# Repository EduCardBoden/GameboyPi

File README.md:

# GameboyPi v1.2 – Raspberry-Pi-Zero-Handheld im Game-Boy-Color-Stil

Tragbarer Retro-Handheld mit eigener Trägerplatine (KiCad 10), 3D-druckbarem Gehäuse (OpenSCAD) und LiPo-Akku.
**Status: Design fertig und rechnerisch geprüft, aber noch nicht gebaut.** Siehe [Prüfstatus](documentation/testing.md) und [offene Risiken](#offene-technische-risiken).

| | |
|---|---|
| Rechner | Raspberry Pi Zero 2 W (Zero W / Zero kompatibel) |
| Display | 2,4" ILI9341 SPI, 320×240 (LAFVIN mit Touch ≈ MSP2402, Touch ungenutzt), 60 fps mit fbcp-ili9341 |
| Bedienung | D-Pad, A, B, Start, Select, Ein/Aus-Schiebeschalter (sicheres Herunterfahren), Lautstärkeknopf |
| Audio | 20-mm-Lautsprecher (PAM8302, 2,5 W) + 3,5-mm-Kopfhörerbuchse mit Lautsprecher-Abschaltung |
| Akku | LiPo 103450, 2000 mAh, PowerBoost 1000C (Micro-USB-Laden, Spielen beim Laden, Lade-LEDs) |
| Laufzeit | ca. 2 h typisch (1,5–2,7 h), [Rechnung](documentation/battery-runtime.md) |
| Gehäuse | 84 × 140 × 29,3 mm (Original-GBC: 78 × 133,5 × 27,4 mm), Design **„GBX – Game Boy Emulator“**: schwarz mit Fasen, Logo in Chrom-Silber/Lila vorne und hinten ([Vorschau](mechanical/previews/design_front.png), [Rückseite](mechanical/previews/design_back.png)) |
| Kosten | ca. 130 € ([Stückliste](bom/bill-of-materials.csv)) |
| Wartung | microSD seitlich, Mini-HDMI + Micro-USB-Daten oben, UART-Konsole (J8), 6 Testpunkte |

## Projektstruktur

```
GameboyPi/
├── README.md                     ← diese Datei
├── ARCHITECTURE.md               ← wie die Generator-Skripte zusammenhängen (Datenfluss, Build)
├── CLAUDE.md                     ← Arbeitsregeln für Claude Code
├── bestellung/                   ← Bestellpaket: Platine (JLCPCB), Bauteile, 3D-Druck (vom Build aktualisiert)
├── bom/bill-of-materials.csv     ← Stückliste mit Bezugsquellen und Preisen
├── electronics/
│   ├── kicad-project/            ← KiCad-Projekt + Generator-Skripte (design.py = zentrale Netzliste)
│   ├── gerber/                   ← Gerber + Bohrdaten + GameboyPi_Gerber.zip (zum Hersteller)
│   ├── schematics/               ← Schaltplan als PDF
│   └── assembly/                 ← Pick&Place-CSV, KiCad-BOM, Bestückungspläne (PDF), 3D-Renderings, STEP
├── mechanical/
│   ├── cad-source/               ← gameboy_pi_case.scad (parametrisch) + build.ps1 (Kollisionsprüfung, STL)
│   │   ├── logo/                 ← GBX-Logo: Originalbild, trace_logo.py (Vektorisierung), gbx_logo.scad
│   │   └── fonts/                ← Michroma (SIL Open Font License) für die Slogans
│   ├── stl/                      ← front, back, dpad, ab, startselect, knob + 4 Logo-Einlagen (silber/lila)
│   ├── step/                     ← dieselben Teile als STEP-Volumenkörper (FreeCAD, nicht im Git)
│   └── previews/                 ← Vorschaubilder
├── software/
│   ├── setup-guide.md            ← RetroPie-Einrichtung, Treiber, Tasten, Audio, Akku, Herunterfahren
│   └── configuration/            ← config.txt-Ergänzung, install.sh, Akku-Dienst
├── documentation/
│   ├── wiring.md                 ← Architektur, GPIO-Belegung, Modul-Pinouts, Abschaltlogik
│   ├── assembly-guide.md         ← Werkzeug, Lötreihenfolge, Druck, Endmontage
│   ├── testing.md                ← durchgeführte Prüfungen + Inbetriebnahme-Messplan
│   └── battery-runtime.md        ← Stromverbrauch, Laufzeit, Lade-/Entladeströme, Kabel
├── tools/freerouting/            ← Autorouter (wird von build.ps1 genutzt)
└── .vscode/                      ← Tasks: Strg+Shift+B baut alles
```

## Bauen (VS Code)

Den Ordner in VS Code öffnen, dann **Strg+Shift+B** („Alles bauen“). Alternativ einzeln über *Terminal → Task ausführen*:

- **Platine bauen (KiCad):** Schaltplan → Platine → Freerouting → ERC/DRC → Gerber, BOM, Pick&Place, PDFs, Renderings (~3 min)
- **Gehäuse bauen (OpenSCAD):** Kollisionsprüfung aller Bauteile gegen die Schalen → STLs → Vorschaubilder
- **Nur STLs exportieren**, **Platine in KiCad öffnen**, **Gehäuse in OpenSCAD öffnen**

Benötigt (installiert): KiCad 10.0, OpenSCAD 2021.01, Java 25 (Microsoft OpenJDK) für Freerouting 2.5.

## Komponenten- und Architekturentscheidungen

| Entscheidung | Begründung |
|---|---|
| **Pi Zero 2 W** kopfüber auf der Platinenrückseite | 4 Kerne (SNES/PS1 flüssig), gleiche Pinbelegung wie Zero/Zero W. Kopfüber wird das Gerät flacher, HDMI/USB zeigen zur Oberkante. |
| **2,4" ILI9341 SPI (LAFVIN ≈ MSP2402)** | Passt in die GBC-Breite. Der Linux-Treiber fbcp-ili9341 ist erprobt (DMA, 60 fps, geringe Latenz). Maße stammen aus der Herstellerzeichnung. Das bestellte Modul hat eine Touch-Folie (ungenutzt), das Gehäuse ist dafür 1,3 mm dicker (`lcd_touch`). |
| **Adafruit PowerBoost 1000C** statt TP4056 + MT3608 | Geprüftes Modul mit Load-Sharing (laden und spielen), festen 5,2 V (kein Einstell-Poti, das ab Werk 12 V liefern kann), EN-Eingang für die Abschaltlogik, LBO-Signal und Lade-LEDs. |
| **Soft-Power mit 2 × BS170** | Der Schalter trennt nicht hart. Er fordert das Herunterfahren an, und der Pi schaltet sich danach selbst ab. Schützt die SD-Karte. |
| **PWM-Audio + PAM8302 + Klinke mit Schaltkontakt** | Ein Audiopfad für beides: Kopfhörer bekommen Line-Pegel, der Lautsprecher bekommt Verstärker und Lautstärkepoti. Ein I2S-Verstärker (v1.0) kann keine Kopfhörer treiben. |
| **ADS1115** an VBAT/2 | Pi hat keinen ADC. Liefert Akkustand in % plus Abschaltung bei leerem Akku. |
| **Nur THT-Bauteile + Module** | Von Hand lötbar, keine SMD-Bestückung beim Hersteller nötig. |

## Stückliste (Kurzfassung, Details in `bom/bill-of-materials.csv`)

| Teil | ca. € |
|---|---|
| Raspberry Pi Zero 2 W (mit Stiftleiste) + 2×20-Buchse + Abstandsbolzen | 22,50 |
| microSD 32 GB | 7,00 |
| Display LAFVIN 2,4" (Touch) + M3-Abstandshalter | 16,80 |
| Adafruit PowerBoost 1000C | 22,00 |
| LiPo 103450 2000 mAh mit Schutz | 10,00 |
| Adafruit PAM8302 + Lautsprecher 20 mm | 7,00 |
| Adafruit ADS1115 | 15,00 |
| Taster, Schalter, Klinke, Poti, MOSFETs, Diode, LED, R/C, Stiftleisten | ≈ 7,20 |
| Leiterplatte (5 Stk. inkl. Versand) | 15,00 |
| Schrauben, Filament, Kleinmaterial, Acrylscheibe | ≈ 6,90 |
| **Summe** | **≈ 130 €** |

## Benötigtes Werkzeug

Temperaturgeregelter Lötkolben + Zinn + Flussmittel, Seitenschneider, Abisolierzange, Pinzette, **Multimeter**, Schraubendreher PH0/PH1, Messschieber, FDM-3D-Drucker. Optional: USB-UART-Adapter (3,3 V), Labornetzteil mit Strombegrenzung. Details in [assembly-guide.md](documentation/assembly-guide.md).

## Montage in Kurzform

1. Platine mit `electronics/gerber/GameboyPi_Gerber.zip` bestellen. Gehäuseteile aus `mechanical/stl/` drucken.
2. Vorderseite bestücken (R, C, LED, Taster, Schalter, Klinke), dann die Rückseite (R, D, Q, C1, Poti, UART, Pi-Buchse, Module).
3. **Inbetriebnahme ohne Pi** nach [testing.md](documentation/testing.md): Testpunkte messen, Abschaltlogik prüfen.
4. Display auf 4-mm-Abstandshalter setzen und verlöten.
5. Tasten, Lautsprecher und Platine in die Vorderschale legen, Akku in den Akkurahmen, Pi aufstecken, Rückschale verschrauben, Knopf aufstecken.
6. Software nach [setup-guide.md](software/setup-guide.md) einrichten.

## Erwartete Akkulaufzeit

≈ **2,1 h** typisch, 2,7 h bei Game Boy/NES mit WLAN aus, 1,5 h unter Dauervolllast. Laden mit 1 A in ≈ 2,5 h, Spielen währenddessen möglich. Rechenweg in [battery-runtime.md](documentation/battery-runtime.md).

## Offene technische Risiken

Ehrliche Liste dessen, was nur rechnerisch geprüft ist oder auf Annahmen beruht. **Vor der Bestellung von 5 Platinen lesen.**

1. **Nicht physisch gebaut oder gemessen.** ERC, DRC, Netzlistenvergleich und die Kollisionsprüfung im CAD sind bestanden. Es gab aber keinen Probedruck, keine Messung und keine Schaltungssimulation (SPICE) der Abschaltlogik.
2. **Soft-Power (v1.2 rechnerisch geklärt):** Die BS170-Schwelle (max. 3,0 V) ist bei **1 mA** Drainstrom spezifiziert (onsemi). Der EN-Pull-up im PowerBoost ist laut Adafruit-Schaltplan **R13 = 200 kΩ an VBAT**, Q1 muss also nur ≈ 21 µA ziehen, ~50× weniger als der Spezifikationsstrom. EN schaltet bei < 0,2 × VBAT ab (TI TPS61090). Restrisiko nur noch im Messplan (Punkt 2.2).
3. **gpio-poweroff:** Das Overlay ist für eine solche Abschaltung gedacht. Das Verhalten hängt aber von der Kernel-Version ab (RetroPie 4.8 / Buster). Falls GPIO4 nach dem Herunterfahren nicht low geht, kann ein systemd-Skript in `/lib/systemd/system-shutdown/` das übernehmen.
4. **PowerBoost-Grenze 1 A:** Geschätzte Spitzenlast ≈ 1 A (Pi-Last + laute Passagen). Seit v1.2 begrenzen R6/R7 = 47 kΩ die Lautsprecherleistung auf ≤ 0,5 W, damit sinkt der Audio-Spitzenstrom von ≈ 330 mA auf ≈ 120 mA (bei 5 V, 85 % Wirkungsgrad). Weitere Gegenmittel: C1 470 µF, WLAN aus.
5. **Gehäusemaße teils angenommen:** Display, Pi, PowerBoost, PAM8302 und ADS1115 stammen aus Herstellerdaten. **Nicht verifiziert** sind die Bauhöhen von Poti PTV09A-2 (≈ 11,5 mm angenommen), Klinke SJ1-3525N (5,2 mm), Elkos und Lautsprecher, ebenso die genaue Lage der PowerBoost-LEDs unter dem Lichtleiter. Die Öffnungen sind großzügig, trotzdem zuerst die Frontschale probedrucken.
6. **Kollisionsprüfung mit Hüllquadern:** Sie prüft vereinfachte Quader gegen die Schalen, keine exakten 3D-Modelle.
7. **Display-Variante:** Das Gehäuse ist auf das LAFVIN-Modul mit Touch-Folie (≈ MSP2402) ausgelegt (`lcd_touch = 1.3` in der `.scad`). Für ein MSP2401 ohne Touch `lcd_touch = 0` setzen und neu bauen. Die Dicke der Touch-Folie ist nur aus dem Produktbild abgeleitet, also vor dem Druck nachmessen. Andere 2,4"-Module (70,5 mm breit) passen nicht.
8. **PWM-Audio:** Leichtes Rauschen ist typisch. Kopfhörerpegel ist Line-Niveau (≈ −12 dB an 32 Ω), also eher leise. Die Kopfhörer-Lautstärke wird nur per Software geregelt, der Knopf regelt nur den Lautsprecher.
9. **Autorouting:** Freerouting hat geroutet. Engstellen gibt es zwischen den Pi-Pins mit 0,15 mm (fertigbar ab 0,127 mm). Ein menschlicher Review des Layouts (z. B. PWM-Audio neben SPI-Takt) ist empfehlenswert.
10. **Wärme:** Der Pi Zero 2 W im geschlossenen Gehäuse kann bei Dauerlast drosseln. Lüftungsschlitze sind vorhanden, eine thermische Simulation fehlt.
11. **Akkuanzeige im Bild** ist nicht umgesetzt (nur `/dev/shm/battery` + automatische Abschaltung). Ein Overlay (z. B. pngview) wäre der nächste Schritt.
12. **Software-Stack:** RetroPie 4.8 basiert auf Debian Buster (nicht mehr gepflegt). fbcp-ili9341 braucht diesen Legacy-Grafikstack. Die Bookworm-Alternative (mipi-dbi-spi) ist dokumentiert, aber langsamer.
13. **Akku-Steckerpolarität:** JST-PH-Akkus gibt es mit vertauschter Belegung. Vor dem Einstecken messen.
14. **Bestückungsdruck:** ca. 100 kosmetische Warnungen (Text auf Pads/Kante). Der Hersteller beschneidet sie, keine Funktion betroffen.
15. **Lieferlage Pi Zero 2 W (Stand 11.11.2026):** Bei BerryBase.at nicht lieferbar, bei Reichelt widersprüchliche Angaben (ein Artikel nennt „lieferbar“, die Shop-Suche „ab 22.12.2026“). Der Pi Zero W (langsamer) passt mechanisch und elektrisch. Details: `documentation/PURCHASING_COMPARISON.md`.
16. **ADS1115-Version:** Die Platine erwartet die Pinbelegung der **STEMMA-QT-Version** von Adafruit #1085. Ältere Lagerware (eine 10-polige Leiste) passt nicht. Vor dem Löten das Modul mit `wiring.md` vergleichen.

## Rechtliches

Nur eigene, rechtmäßig erworbene Spiele und BIOS-Dateien verwenden. Das Gehäuse ist vom Game Boy Color *inspiriert* und trägt das eigene „GBX“-Logo. Der Slogan „GAME BOY EMULATOR“ enthält die Marke „Game Boy“ (Nintendo). Für ein privates Einzelstück ist das unproblematisch. Wer Gehäuse oder Geräte verkaufen will, sollte den Slogan in `gameboy_pi_case.scad` (`back_silver_2d`) ändern.

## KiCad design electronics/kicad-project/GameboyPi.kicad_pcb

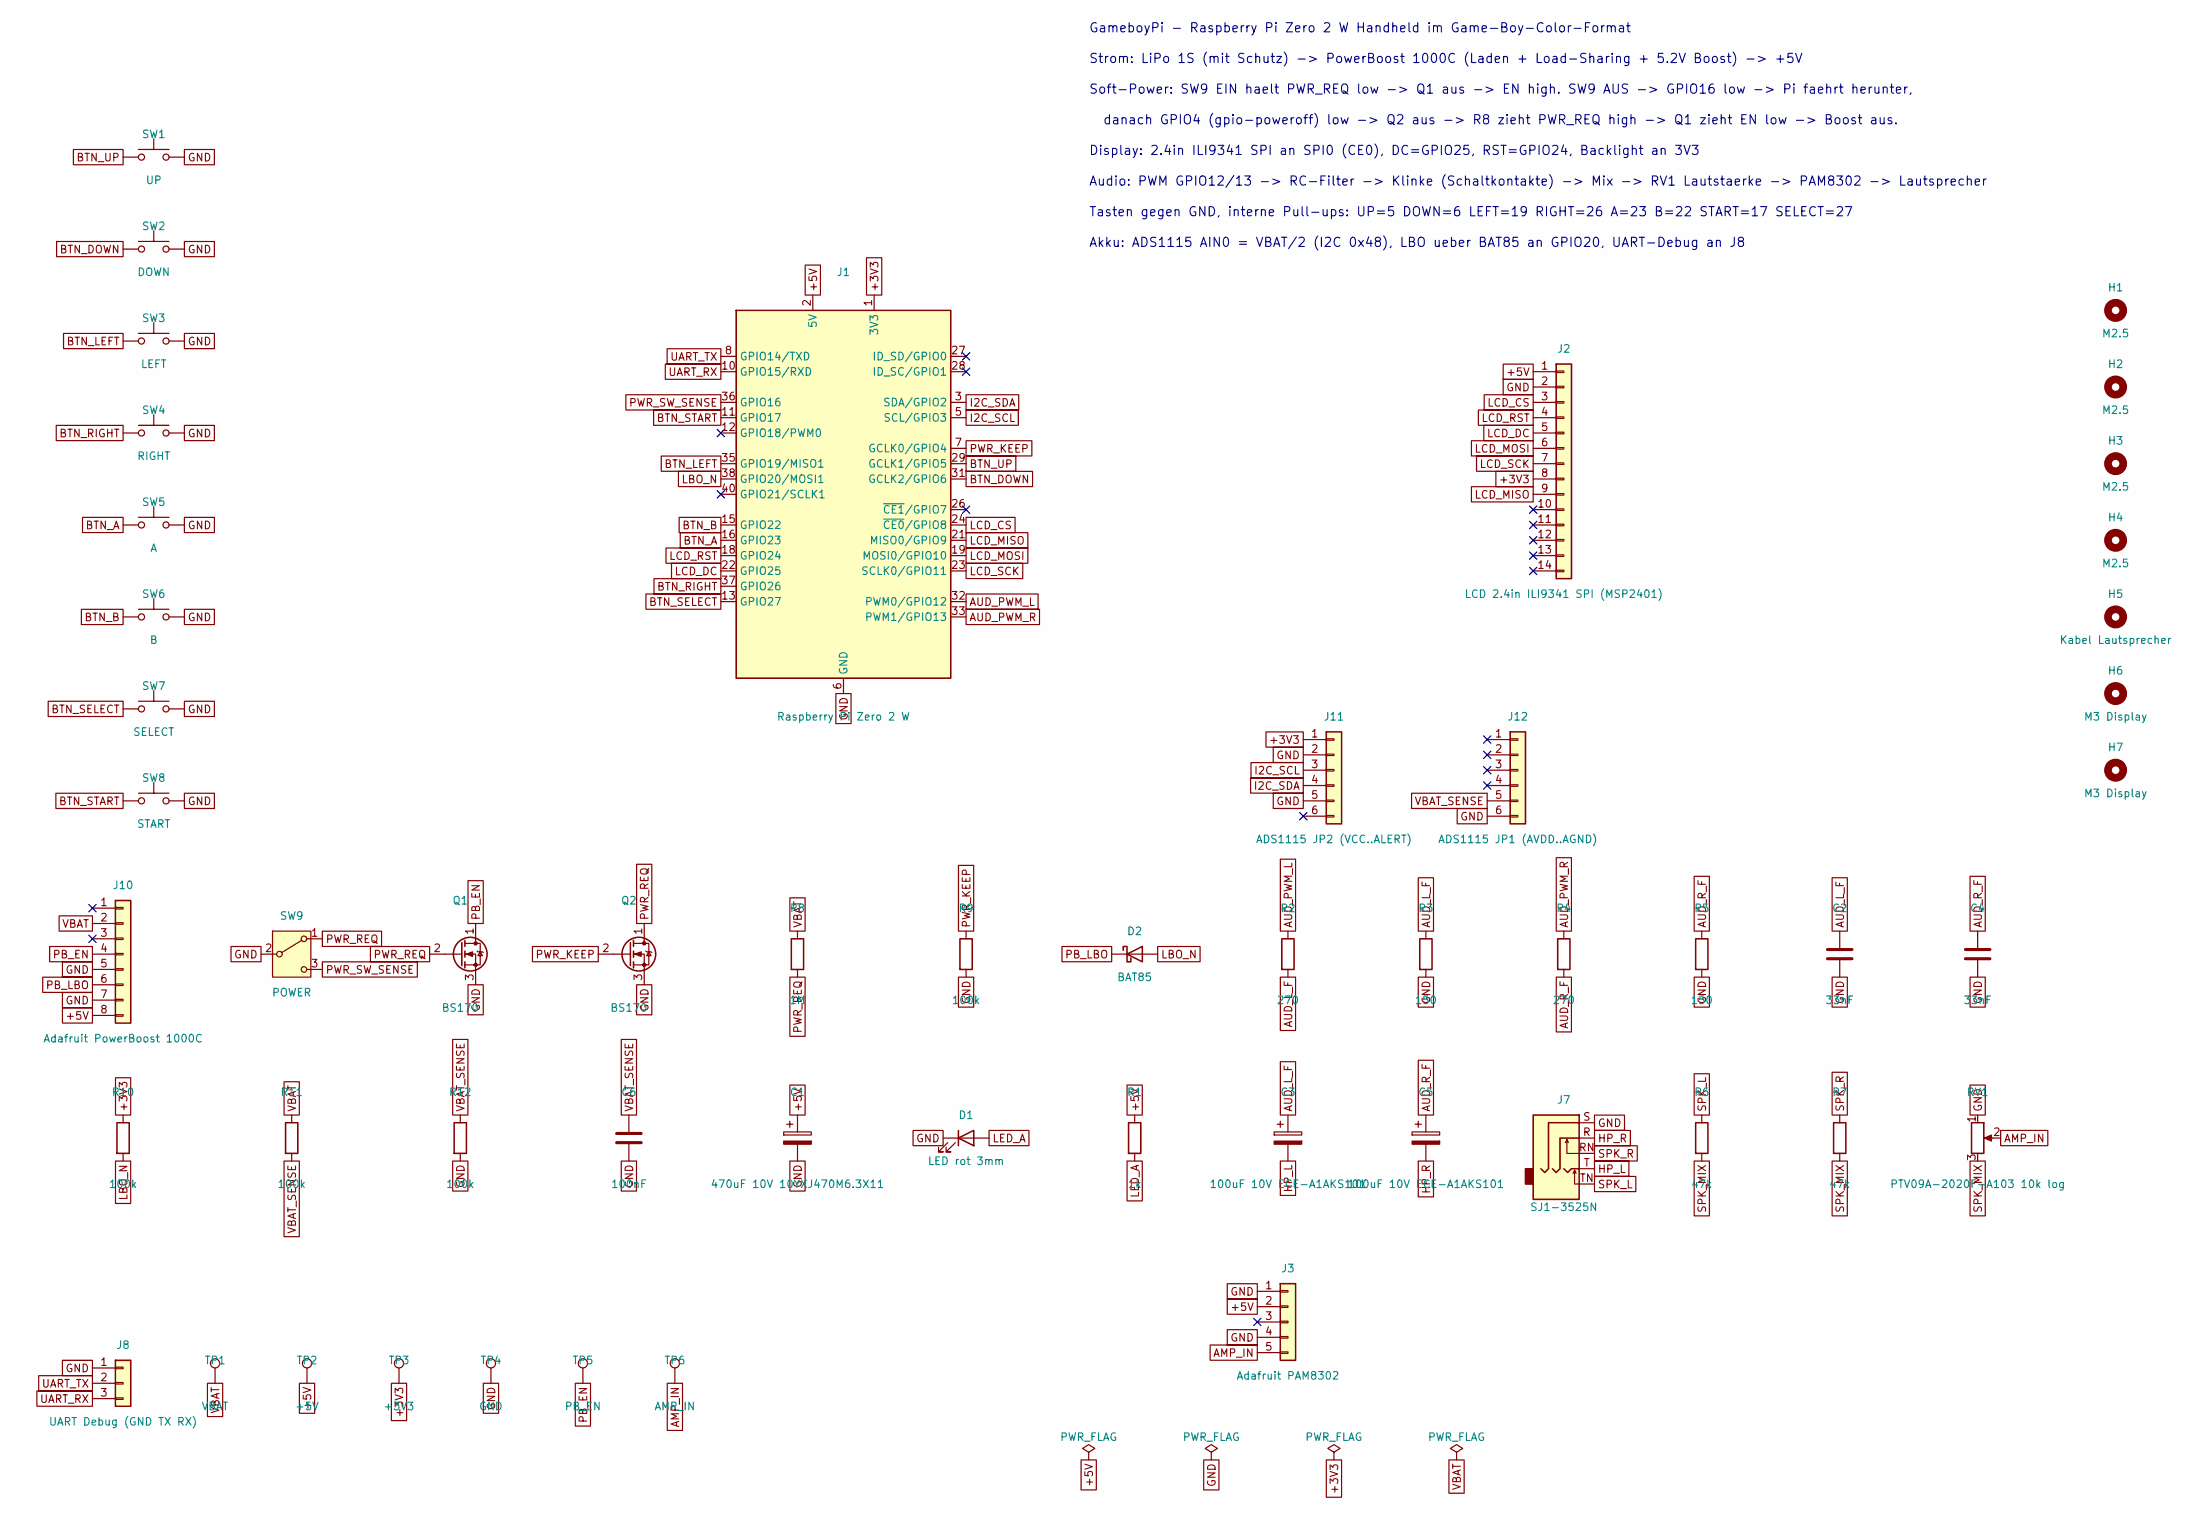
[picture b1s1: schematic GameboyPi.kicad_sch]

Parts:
C1: 470uF 10V 10YXJ470M6.3X11; CP_Radial_D6.3mm_P2.50mm
C2, C4: 33nF; C_Disc_D3.0mm_W1.6mm_P2.50mm
C3, C5: 100uF 10V ECE-A1AKS101; CP_Radial_D6.3mm_P2.50mm
C6: 100nF; C_Disc_D3.0mm_W1.6mm_P2.50mm
D1: LED rot 3mm; LED_D3.0mm
D2: BAT85; D_DO-35_SOD27_P7.62mm_Horizontal
H1, H2, H3, H4: M2.5; MountingHole_2.7mm_M2.5
H5: Kabel Lautsprecher; MountingHole_3.2mm_M3
H6, H7: M3 Display; MountingHole_3.2mm_M3
J1: Raspberry Pi Zero 2 W; Raspberry_Pi_Zero_Socketed_THT_FaceDown_MountingHoles
J2: LCD 2.4in ILI9341 SPI (MSP2401); PinHeader_1x14_P2.54mm_Vertical
J3: Adafruit PAM8302; PinHeader_1x05_P2.54mm_Vertical
J7: SJ1-3525N; Jack_3.5mm_CUI_SJ1-3525N_Horizontal
J8: UART Debug (GND TX RX); PinHeader_1x03_P2.54mm_Vertical
J10: Adafruit PowerBoost 1000C; PinHeader_1x08_P2.54mm_Vertical
J11: ADS1115 JP2 (VCC..ALERT); PinHeader_1x06_P2.54mm_Vertical
J12: ADS1115 JP1 (AVDD..AGND); PinHeader_1x06_P2.54mm_Vertical
Q1, Q2: BS170; TO-92_Inline_Wide
R1: 1k; R_Axial_DIN0207_L6.3mm_D2.5mm_P7.62mm_Horizontal
R2, R4: 270; R_Axial_DIN0207_L6.3mm_D2.5mm_P7.62mm_Horizontal
R3, R5: 150; R_Axial_DIN0207_L6.3mm_D2.5mm_P7.62mm_Horizontal
R6, R7: 47k; R_Axial_DIN0207_L6.3mm_D2.5mm_P7.62mm_Horizontal
R8: 1M; R_Axial_DIN0207_L6.3mm_D2.5mm_P7.62mm_Horizontal
R9, R10, R11, R12: 100k; R_Axial_DIN0207_L6.3mm_D2.5mm_P7.62mm_Horizontal
RV1: PTV09A-2020F-A103 10k log; Potentiometer_Bourns_PTV09A-2_Single_Horizontal
SW1: UP; SW_PUSH_6mm
SW2: DOWN; SW_PUSH_6mm
SW3: LEFT; SW_PUSH_6mm
SW4: RIGHT; SW_PUSH_6mm
SW5: A; SW_PUSH_6mm
SW6: B; SW_PUSH_6mm
SW7: SELECT; SW_PUSH_6mm
SW8: START; SW_PUSH_6mm
SW9: POWER; SW_Slide_SPDT_Angled_CK_OS102011MA1Q
TP1: VBAT; TestPoint_THTPad_D1.5mm_Drill0.7mm
TP2: +5V; TestPoint_THTPad_D1.5mm_Drill0.7mm
TP3: +3V3; TestPoint_THTPad_D1.5mm_Drill0.7mm
TP4: GND; TestPoint_THTPad_D1.5mm_Drill0.7mm
TP5: PB_EN; TestPoint_THTPad_D1.5mm_Drill0.7mm
TP6: AMP_IN; TestPoint_THTPad_D1.5mm_Drill0.7mm

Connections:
+3V3: J1.1 (3V3), J1.17 (3V3), J2.8, J11.1, R10.1, TP3.1
+5V: C1.1, J1.2 (5V), J1.4 (5V), J2.1, J3.2, J10.8, R1.1, TP2.1
AMP_IN: J3.5, RV1.2, TP6.1
AUD_L_F: C2.1, C3.1, R2.2, R3.1
AUD_PWM_L: J1.32 (PWM0/GPIO12), R2.1
AUD_PWM_R: J1.33 (PWM1/GPIO13), R4.1
AUD_R_F: C4.1, C5.1, R4.2, R5.1
BTN_A: J1.16 (GPIO23), SW5.1
BTN_B: J1.15 (GPIO22), SW6.1
BTN_DOWN: J1.31 (GCLK2/GPIO6), SW2.1
BTN_LEFT: J1.35 (GPIO19/MISO1), SW3.1
BTN_RIGHT: J1.37 (GPIO26), SW4.1
BTN_SELECT: J1.13 (GPIO27), SW7.1
BTN_START: J1.11 (GPIO17), SW8.1
BTN_UP: J1.29 (GCLK1/GPIO5), SW1.1
GND: C1.2, C2.2, C4.2, C6.2, D1.1 (K), J1.6 (GND), J1.9 (GND), J1.14 (GND), J1.20 (GND), J1.25 (GND), J1.30 (GND), J1.34 (GND), J1.39 (GND), J2.2, J3.1, J3.4, J7.S, J8.1, J10.5, J10.7, J11.2, J11.5, J12.6, Q1.3 (S), Q2.3 (S), R3.2, R5.2, R9.2, R12.2, RV1.1, SW1.2, SW2.2, SW3.2, SW4.2, SW5.2, SW6.2, SW7.2, SW8.2, SW9.2 (B), TP4.1
HP_L: C3.2, J7.T
HP_R: C5.2, J7.R
I2C_SCL: J1.5 (SCL/GPIO3), J11.3
I2C_SDA: J1.3 (SDA/GPIO2), J11.4
LBO_N: D2.2 (A), J1.38 (GPIO20/MOSI1), R10.2
LCD_CS: J1.24 (~CE0/GPIO8), J2.3
LCD_DC: J1.22 (GPIO25), J2.5
LCD_MISO: J1.21 (MISO0/GPIO9), J2.9
LCD_MOSI: J1.19 (MOSI0/GPIO10), J2.6
LCD_RST: J1.18 (GPIO24), J2.4
LCD_SCK: J1.23 (SCLK0/GPIO11), J2.7
LED_A: D1.2 (A), R1.2
PB_EN: J10.4, Q1.1 (D), TP5.1
PB_LBO: D2.1 (K), J10.6
PWR_KEEP: J1.7 (GCLK0/GPIO4), Q2.2 (G), R9.1
PWR_REQ: Q1.2 (G), Q2.1 (D), R8.2, SW9.1 (A)
PWR_SW_SENSE: J1.36 (GPIO16), SW9.3 (C)
SPK_L: J7.TN, R6.1
SPK_MIX: R6.2, R7.2, RV1.3
SPK_R: J7.RN, R7.1
UART_RX: J1.10 (GPIO15/RXD), J8.3
UART_TX: J1.8 (GPIO14/TXD), J8.2
VBAT: J10.2, R8.1, R11.1, TP1.1
VBAT_SENSE: C6.1, J12.5, R11.2, R12.1

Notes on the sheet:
GameboyPi - Raspberry Pi Zero 2 W Handheld im Game-Boy-Color-Format
Strom: LiPo 1S (mit Schutz) -> PowerBoost 1000C (Laden + Load-Sharing + 5.2V Boost) -> +5V
Soft-Power: SW9 EIN haelt PWR_REQ low -> Q1 aus -> EN high. SW9 AUS -> GPIO16 low -> Pi faehrt herunter,
danach GPIO4 (gpio-poweroff) low -> Q2 aus -> R8 zieht PWR_REQ high -> Q1 zieht EN low -> Boost aus.
Display: 2.4in ILI9341 SPI an SPI0 (CE0), DC=GPIO25, RST=GPIO24, Backlight an 3V3
Audio: PWM GPIO12/13 -> RC-Filter -> Klinke (Schaltkontakte) -> Mix -> RV1 Lautstaerke -> PAM8302 -> Lautsprecher
Tasten gegen GND, interne Pull-ups: UP=5 DOWN=6 LEFT=19 RIGHT=26 A=23 B=22 START=17 SELECT=27
Akku: ADS1115 AIN0 = VBAT/2 (I2C 0x48), LBO ueber BAT85 an GPIO20, UART-Debug an J8

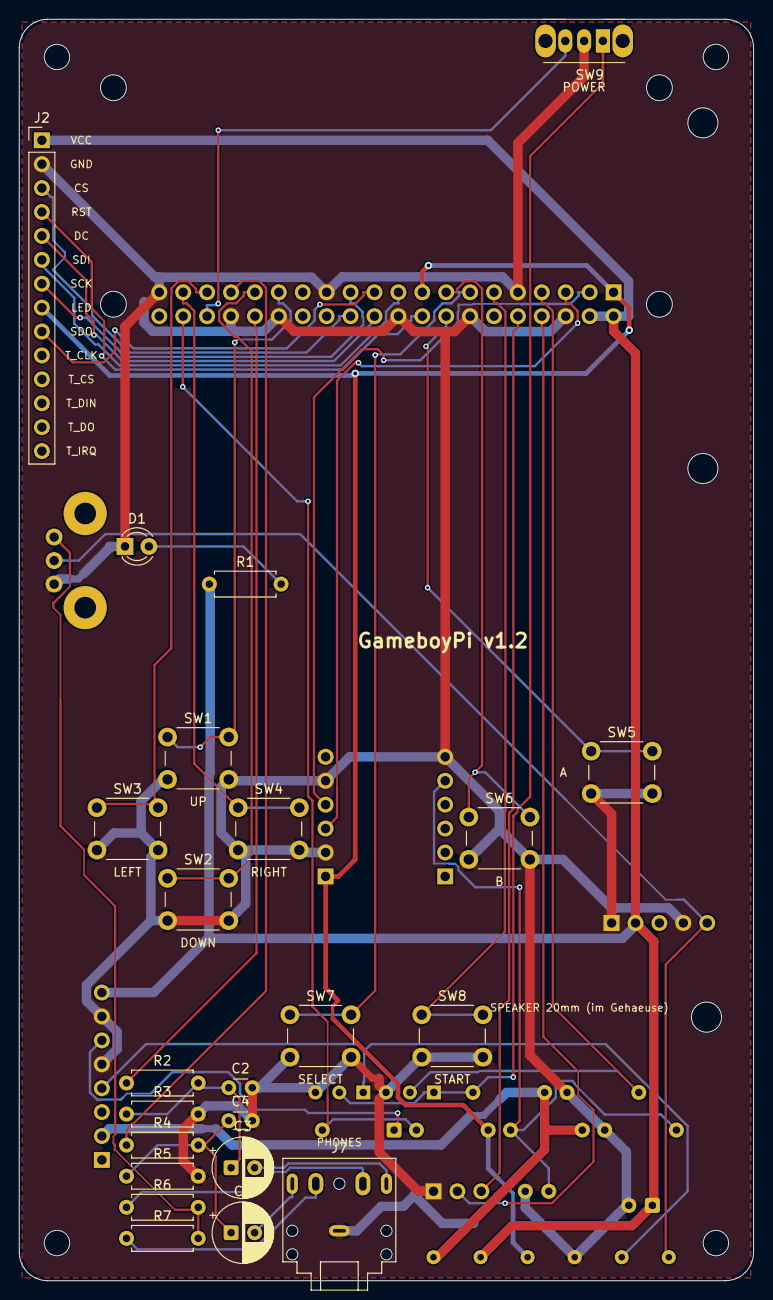
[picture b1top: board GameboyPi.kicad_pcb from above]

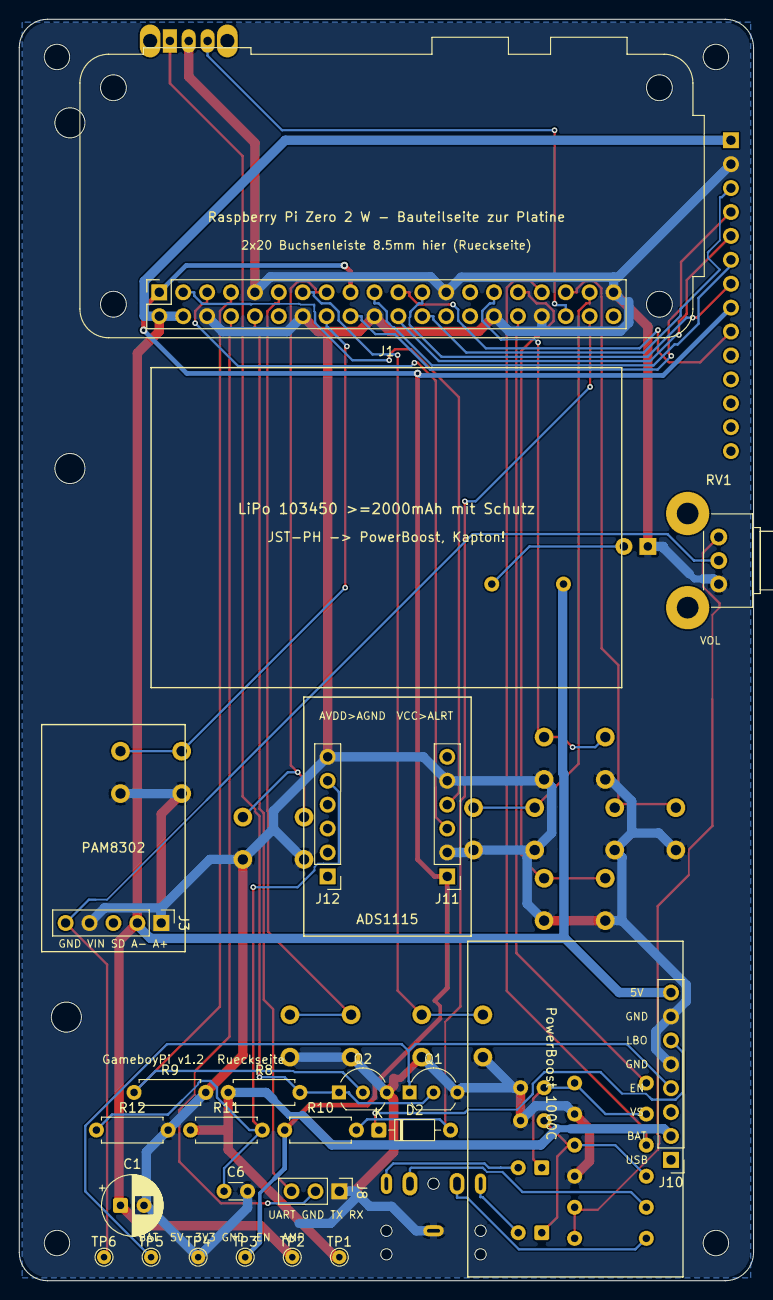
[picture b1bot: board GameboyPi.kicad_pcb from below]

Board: 2 copper layers, 78.0 x 134.0 mm, 53 parts (23 on the bottom side), 40 nets.

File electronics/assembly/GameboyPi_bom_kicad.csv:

"Reference","Value","Footprint","QUANTITY"
"C1","470uF 10V 10YXJ470M6.3X11","Capacitor_THT:CP_Radial_D6.3mm_P2.50mm","1"
"C2,C4","33nF","Capacitor_THT:C_Disc_D3.0mm_W1.6mm_P2.50mm","2"
"C3,C5","100uF 10V ECE-A1AKS101","Capacitor_THT:CP_Radial_D6.3mm_P2.50mm","2"
"C6","100nF","Capacitor_THT:C_Disc_D3.0mm_W1.6mm_P2.50mm","1"
"D1","LED rot 3mm","LED_THT:LED_D3.0mm","1"
"D2","BAT85","Diode_THT:D_DO-35_SOD27_P7.62mm_Horizontal","1"
"J1","Raspberry Pi Zero 2 W","Module:Raspberry_Pi_Zero_Socketed_THT_FaceDown_MountingHoles","1"
"J2","LCD 2.4in ILI9341 SPI (MSP2401)","Connector_PinHeader_2.54mm:PinHeader_1x14_P2.54mm_Vertical","1"
"J3","Adafruit PAM8302","Connector_PinHeader_2.54mm:PinHeader_1x05_P2.54mm_Vertical","1"
"J7","SJ1-3525N","Connector_Audio:Jack_3.5mm_CUI_SJ1-3525N_Horizontal","1"
"J8","UART Debug (GND TX RX)","Connector_PinHeader_2.54mm:PinHeader_1x03_P2.54mm_Vertical","1"
"J10","Adafruit PowerBoost 1000C","Connector_PinHeader_2.54mm:PinHeader_1x08_P2.54mm_Vertical","1"
"J11","ADS1115 JP2 (VCC..ALERT)","Connector_PinHeader_2.54mm:PinHeader_1x06_P2.54mm_Vertical","1"
"J12","ADS1115 JP1 (AVDD..AGND)","Connector_PinHeader_2.54mm:PinHeader_1x06_P2.54mm_Vertical","1"
"Q1,Q2","BS170","Package_TO_SOT_THT:TO-92_Inline_Wide","2"
"R1","1k","Resistor_THT:R_Axial_DIN0207_L6.3mm_D2.5mm_P7.62mm_Horizontal","1"
"R2,R4","270","Resistor_THT:R_Axial_DIN0207_L6.3mm_D2.5mm_P7.62mm_Horizontal","2"
"R3,R5","150","Resistor_THT:R_Axial_DIN0207_L6.3mm_D2.5mm_P7.62mm_Horizontal","2"
"R6,R7","47k","Resistor_THT:R_Axial_DIN0207_L6.3mm_D2.5mm_P7.62mm_Horizontal","2"
"R8","1M","Resistor_THT:R_Axial_DIN0207_L6.3mm_D2.5mm_P7.62mm_Horizontal","1"
"R9-R12","100k","Resistor_THT:R_Axial_DIN0207_L6.3mm_D2.5mm_P7.62mm_Horizontal","4"
"RV1","PTV09A-2020F-A103 10k log","Potentiometer_THT:Potentiometer_Bourns_PTV09A-2_Single_Horizontal","1"
"SW1","UP","Button_Switch_THT:SW_PUSH_6mm","1"
"SW2","DOWN","Button_Switch_THT:SW_PUSH_6mm","1"
"SW3","LEFT","Button_Switch_THT:SW_PUSH_6mm","1"
"SW4","RIGHT","Button_Switch_THT:SW_PUSH_6mm","1"
"SW5","A","Button_Switch_THT:SW_PUSH_6mm","1"
"SW6","B","Button_Switch_THT:SW_PUSH_6mm","1"
"SW7","SELECT","Button_Switch_THT:SW_PUSH_6mm","1"
"SW8","START","Button_Switch_THT:SW_PUSH_6mm","1"
"SW9","POWER","Button_Switch_THT:SW_Slide_SPDT_Angled_CK_OS102011MA1Q","1"
"TP1","VBAT","TestPoint:TestPoint_THTPad_D1.5mm_Drill0.7mm","1"
"TP2","+5V","TestPoint:TestPoint_THTPad_D1.5mm_Drill0.7mm","1"
"TP3","+3V3","TestPoint:TestPoint_THTPad_D1.5mm_Drill0.7mm","1"
"TP4","GND","TestPoint:TestPoint_THTPad_D1.5mm_Drill0.7mm","1"
"TP5","PB_EN","TestPoint:TestPoint_THTPad_D1.5mm_Drill0.7mm","1"
"TP6","AMP_IN","TestPoint:TestPoint_THTPad_D1.5mm_Drill0.7mm","1"

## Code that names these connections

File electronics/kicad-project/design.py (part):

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    1: "+3V3", 17: "+3V3",
    2: "+5V", 4: "+5V",
    6: "GND", 9: "GND", 14: "GND", 20: "GND", 25: "GND", 30: "GND", 34: "GND", 39: "GND",
    3: "I2C_SDA",       # GPIO2  – ADS1115
    5: "I2C_SCL",       # GPIO3
    7: "PWR_KEEP",      # GPIO4  – gpio-poweroff: high solange Linux läuft
    8: "UART_TX",       # GPIO14 – Debug-Konsole
    10: "UART_RX",      # GPIO15
    36: "PWR_SW_SENSE", # GPIO16 – gpio-shutdown: low = Schalter auf AUS
    38: "LBO_N",        # GPIO20 – Akku < 3.2 V (PowerBoost LBO)
    # Tasten (interne Pull-ups, gpio-key Overlay)
    29: "BTN_UP",       # GPIO5
    31: "BTN_DOWN",     # GPIO6
    35: "BTN_LEFT",     # GPIO19
    37: "BTN_RIGHT",    # GPIO26
    16: "BTN_A",        # GPIO23
    15: "BTN_B",        # GPIO22
    11: "BTN_START",    # GPIO17
    13: "BTN_SELECT",   # GPIO27
    # Display ILI9341 an SPI0
    19: "LCD_MOSI",     # GPIO10
    21: "LCD_MISO",     # GPIO9
    23: "LCD_SCK",      # GPIO11
    24: "LCD_CS",       # GPIO8 / CE0
    22: "LCD_DC",       # GPIO25
    18: "LCD_RST",      # GPIO24
    # Audio PWM (audremap pins_12_13)
    32: "AUD_PWM_L",    # GPIO12
    33: "AUD_PWM_R",    # GPIO13
}

BUTTONS = [
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part("D2", "Device:D_Schottky", "BAT85", "Diode_THT:D_DO-35_SOD27_P7.62mm_Horizontal",
     {1: "PB_LBO", 2: "LBO_N"}, pos=(36.0, 118.0), side="B", group="power")
# v1.2: 100k statt 10k. LBO des TPS61090 ist Open-Drain, max. 100 uA Low-Strom (TI-Datenblatt).
# 10k zogen ~0.3 mA. Mit 100k: (3.3 V - 0.25 V) / 100k = 31 uA. GPIO20-Pull im Pi ist aus (config.txt).
part("R10", "Device:R", "100k", R_AX, {1: "+3V3", 2: "LBO_N"}, pos=(46.0, 118.0), side="B", group="power")
# Akkuspannungsmessung: 100k/100k -> max. 2.1 V am ADS1115 AIN0
part("R11", "Device:R", "100k", R_AX, {1: "VBAT", 2: "VBAT_SENSE"}, pos=(56.0, 118.0), side="B", group="power")
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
